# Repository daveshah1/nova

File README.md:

nova
====

This is the primary git repository for Team Nova's CanSat project, containing base station software, rover software, electronics and CAD data.

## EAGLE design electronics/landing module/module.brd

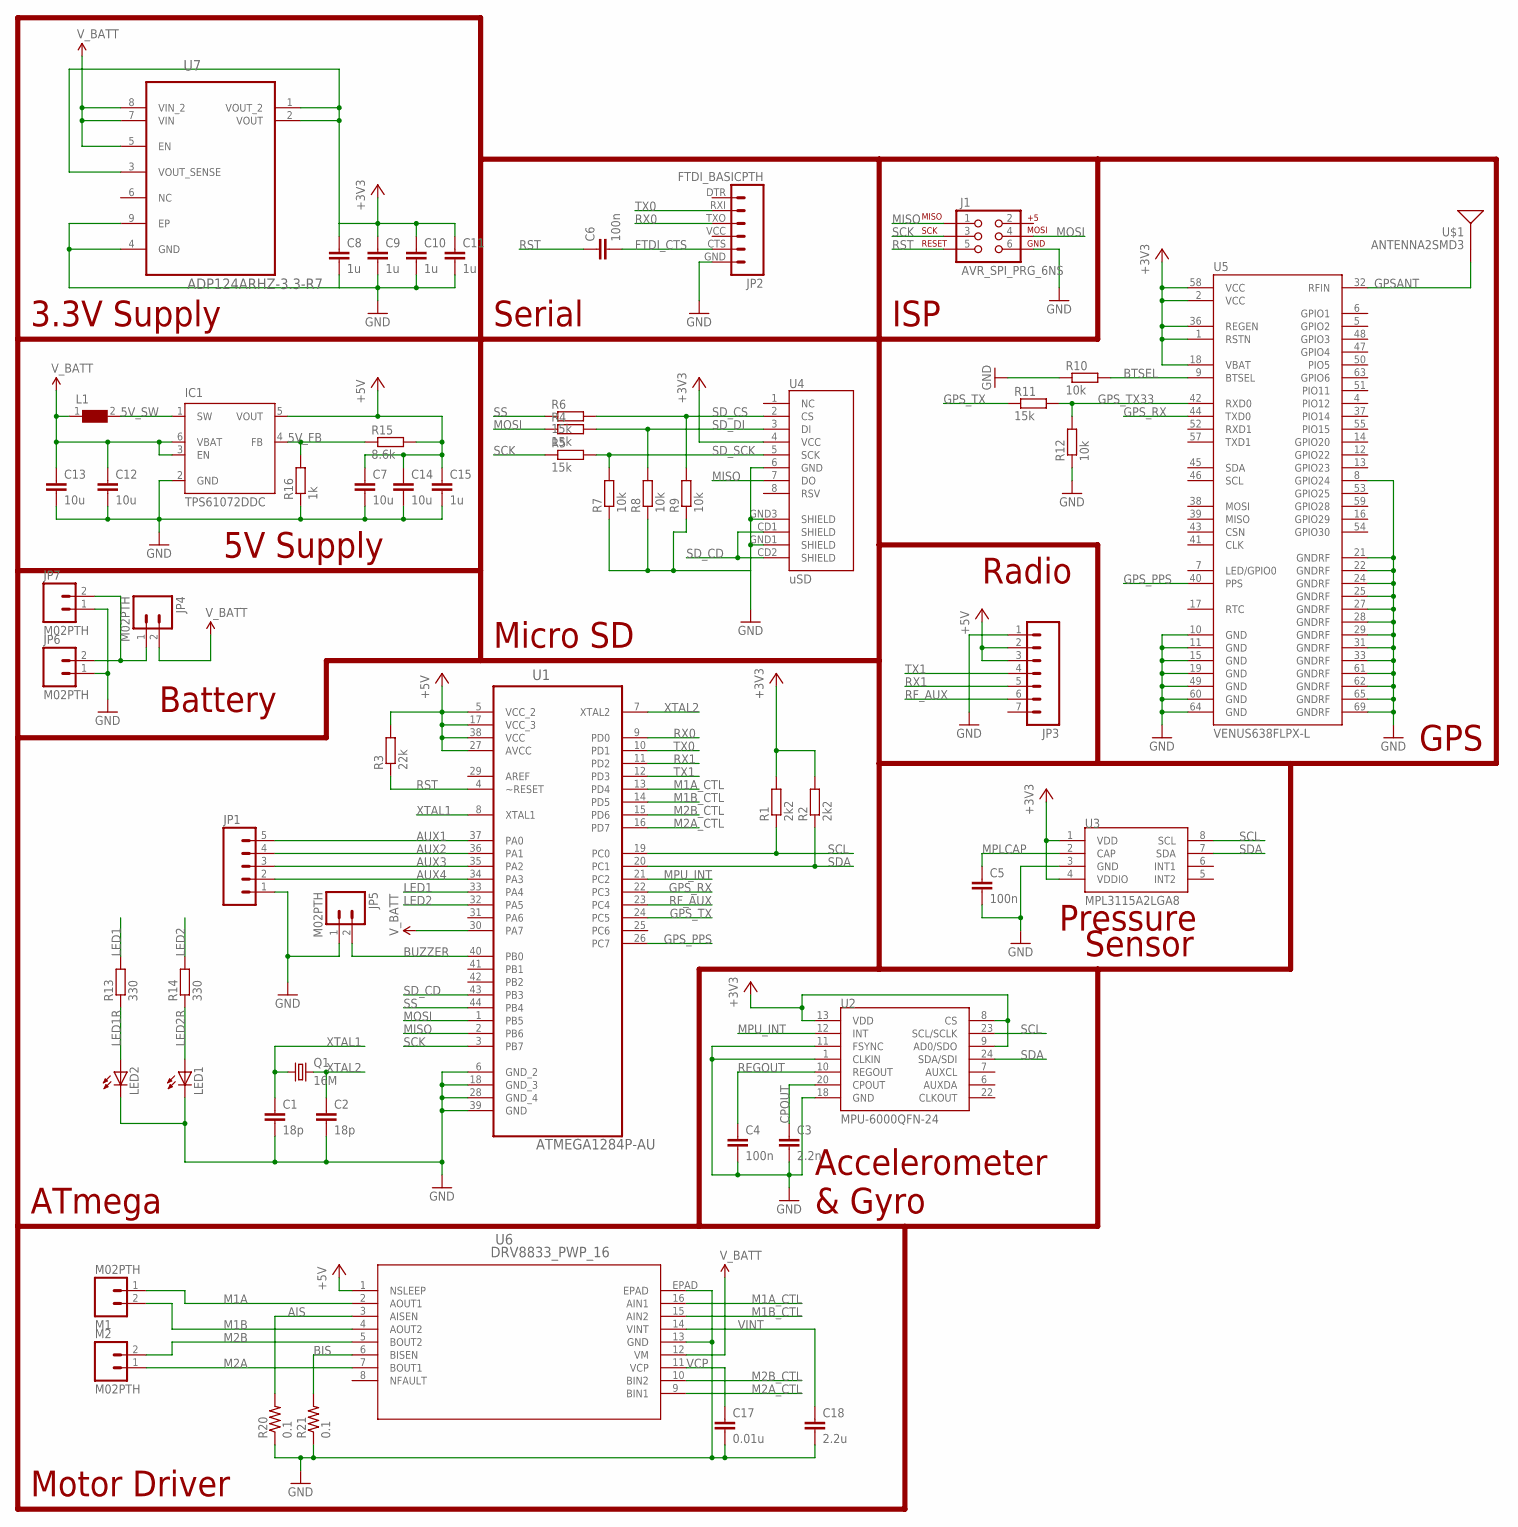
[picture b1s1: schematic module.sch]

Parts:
C1, C2: 18p; C0805
C3: 2.2n; C0805
C4, C5, C6: 100n; C0805
C7, C12, C13, C14: 10u; C0805
C8, C9, C10, C11: 1u; C0603
C15: 1u; C0805
C17: 0.01u; 0805
C18: 2.2u; 0805
IC1: TPS61072DDC; TSOT23-6_DDC
J1: AVR_SPI_PRG_6NS; 2X3-NS
JP1: M05PTH; 1X05
JP2: FTDI_BASICPTH; FTDI_BASIC
JP3: M07; 1X07
JP4, JP5, JP6, JP7: M02PTH; 1X02
L1: WE-TPC-744031004_3816; WE-TPC_3816
LED1, LED2: LEDCHIPLED_0805; CHIPLED_0805
M1, M2: M02PTH; 1X02
Q1: 16M; HC49UP
R1, R2: 2k2; R0805
R3: 22k; R0805
R4, R5, R6, R11: 15k; R0805
R7, R8, R9, R10, R12: 10k; R0805
R13, R14: 330; R0805
R15: 8.6k; R0805
R16: 1k; R0805
R20, R21: 0.1; 1206
U1: ATMEGA1284P-AU; QFP80P1200X1200X120-44N
U2: MPU-6000QFN-24; QFN-24-TESTING
U3: MPL3115A2LGA8; LGA8
U4: uSD; MICRO-SD-SOCKET-PP
U5: VENUS638FLPX-L; VENUS638FLPX
U6: DRV8833_PWP_16; PWP16_2P31X2P46
U7: ADP124ARHZ-3.3-R7; SOP65P490X110-9N
U$1: ANTENNA2SMD3; ANTENNA-CHIP4

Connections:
5V_FB: IC1.4 (FB), R15.1, R16.2
5V_SW: IC1.1 (SW), L1.2
+3V3: C8.1, C9.1, C10.1, C11.1, R1.2, R2.2, U2.8 (CS), U2.9 (AD0/SDO), U2.13 (VDD), U3.1 (VDD), U3.4 (VDDIO), U4.4 (VCC), U5.1 (RSTN), U5.2 (VCC), U5.18 (VBAT), U5.36 (REGEN), U5.58 (VCC), U7.1 (VOUT_2), U7.2 (VOUT), U7.3 (VOUT_SENSE)
+5V: C7.1, C14.1, C15.1, IC1.5 (VOUT), JP3.2, JP3.3, R3.2, R15.2, U1.5 (VCC_2), U1.17 (VCC_3), U1.27 (AVCC), U1.38 (VCC), U6.1 (NSLEEP)
AIS: R20.2, U6.3 (AISEN)
AUX1: JP1.5, U1.37 (PA0)
AUX2: JP1.4, U1.36 (PA1)
AUX3: JP1.3, U1.35 (PA2)
AUX4: JP1.2, U1.34 (PA3)
BIS: R21.2, U6.6 (BISEN)
BTSEL: R10.2, U5.9 (BTSEL)
BUZZER: JP5.2, U1.40 (PB0)
CPOUT: C3.1, U2.20 (CPOUT)
FTDI_CTS: C6.2, JP2.CTS (5)
GND: C1.2, C2.2, C3.2, C4.2, C5.2, C7.2, C8.2, C9.2, C10.2, C11.2, C12.2, C13.2, C14.2, C15.2, C17.2, C18.2, IC1.2 (GND), J1.6, JP1.1, JP2.GND (6), JP3.1, JP5.1, JP6.1, JP7.1, LED1.C, LED2.C, R7.1, R8.1, R9.1, R10.1, R12.1, R16.1, R20.1, R21.1, U1.6 (GND_2), U1.18 (GND_3), U1.28 (GND_4), U1.39 (GND), U2.1 (CLKIN), U2.11 (FSYNC), U2.18 (GND), U3.3 (GND), U4.6 (GND), U4.GND1 (SHIELD), U4.GND3 (SHIELD), U5.8 (GPIO24), U5.10 (GND), U5.11 (GND), U5.15 (GND), U5.19 (GND), U5.21 (GNDRF), U5.22 (GNDRF), U5.24 (GNDRF), U5.25 (GNDRF), U5.27 (GNDRF), U5.28 (GNDRF), U5.29 (GNDRF), U5.31 (GNDRF), U5.33 (GNDRF), U5.49 (GND), U5.60 (GND), U5.61 (GNDRF), U5.62 (GNDRF), U5.64 (GND), U5.65 (GNDRF), U5.69 (GNDRF), U6.13 (GND), U6.EPAD, U7.4 (GND), U7.9 (EP)
GPSANT: U5.32 (RFIN), U$1.SIG
GPS_PPS: U1.26 (PC7), U5.40 (PPS)
GPS_RX: U1.22 (PC3), U5.44 (TXD0)
GPS_TX: R11.1, U1.24 (PC5)
GPS_TX33: R11.2, R12.2, U5.42 (RXD0)
LED1: R13.2, U1.33 (PA4)
LED1R: LED2.A, R13.1
LED2: R14.2, U1.32 (PA5)
LED2R: LED1.A, R14.1
M1A: M1.1, U6.2 (AOUT1)
M1A_CTL: U1.13 (PD4), U6.16 (AIN1)
M1B: M1.2, U6.4 (AOUT2)
M1B_CTL: U1.14 (PD5), U6.15 (AIN2)
M2A: M2.1, U6.7 (BOUT1)
M2A_CTL: U1.16 (PD7), U6.9 (BIN1)
M2B: M2.2, U6.5 (BOUT2)
M2B_CTL: U1.15 (PD6), U6.10 (BIN2)
MISO: J1.1, U1.2 (PB6), U4.7 (DO)
MOSI: J1.4, R4.1, U1.1 (PB5)
MPLCAP: C5.1, U3.2 (CAP)
MPU_INT: U1.21 (PC2), U2.12 (INT)
unnamed: JP4.1, JP6.2, JP7.2
REGOUT: C4.1, U2.10 (REGOUT)
RF_AUX: JP3.6, U1.23 (PC4)
RST: C6.1, J1.5, R3.1, U1.4 (~RESET)
RX0: JP2.TXO (3), U1.9 (PD0)
RX1: JP3.5, U1.11 (PD2)
SCK: J1.3, R5.1, U1.3 (PB7)
SCL: R1.1, U1.19 (PC0), U2.23 (SCL/SCLK), U3.8 (SCL)
SDA: R2.1, U1.20 (PC1), U2.24 (SDA/SDI), U3.7 (SDA)
SD_CD: U1.43 (PB3), U4.CD1 (SHIELD), U4.CD2 (SHIELD)
SD_CS: R6.2, R9.2, U4.2 (CS)
SD_DI: R4.2, R8.2, U4.3 (DI)
SD_SCK: R5.2, R7.2, U4.5 (SCK)
SS: R6.1, U1.44 (PB4)
TX0: JP2.RXI (2), U1.10 (PD1)
TX1: JP3.4, U1.12 (PD3)
VCP: C17.1, U6.11 (VCP)
VINT: C18.1, U6.14 (VINT)
V_BATT: C12.1, C13.1, IC1.3 (EN), IC1.6 (VBAT), JP4.2, L1.1, U1.30 (PA7), U6.12 (VM), U7.5 (EN), U7.7 (VIN), U7.8 (VIN_2)
XTAL1: C1.1, Q1.1, U1.8 (XTAL1)
XTAL2: C2.1, Q1.2, U1.7 (XTAL2)

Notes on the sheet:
Motor Driver
ATmega
Pressure
Sensor
GPS
Radio
Micro SD
Battery
5V Supply
3.3V Supply
Serial
ISP
Accelerometer & Gyro

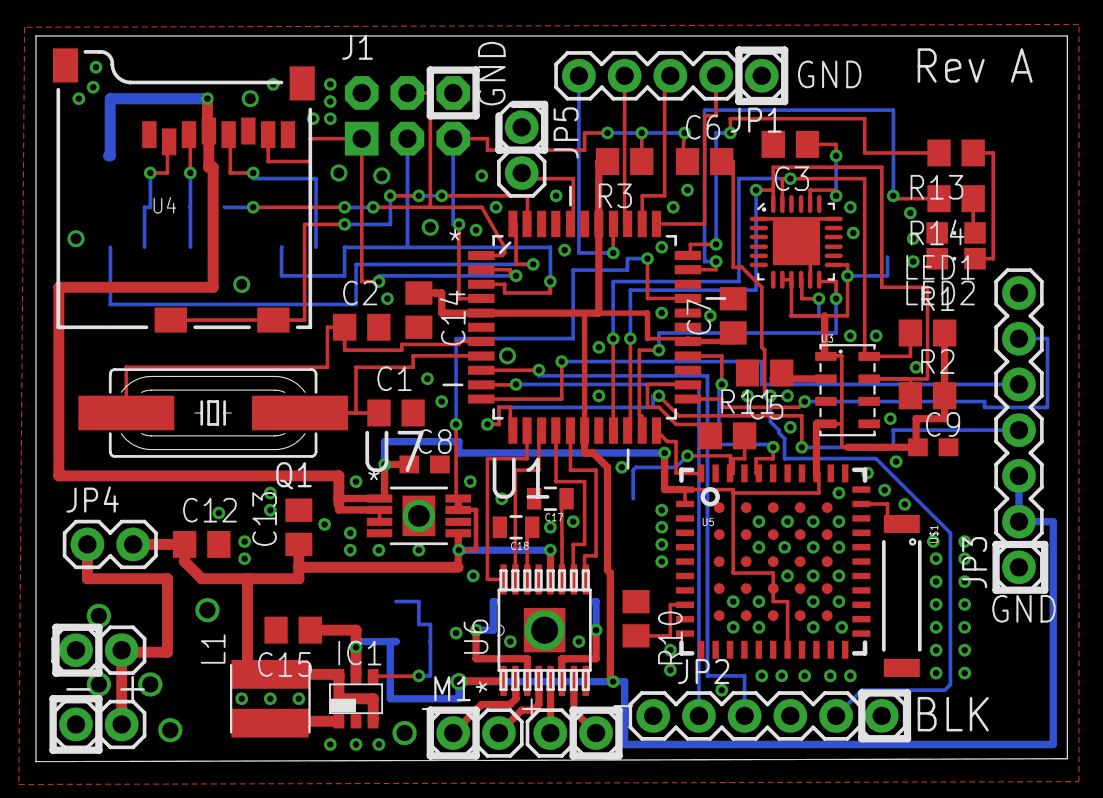
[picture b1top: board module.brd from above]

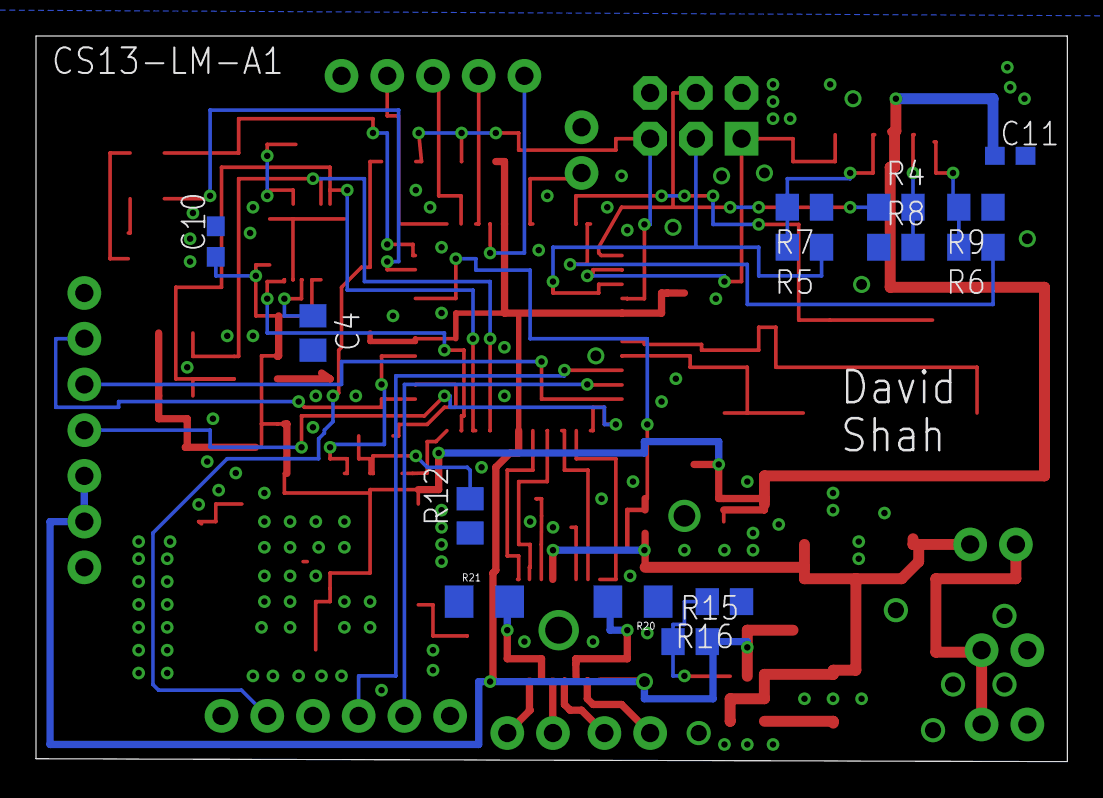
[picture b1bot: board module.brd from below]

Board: 2 copper layers, 57.3 x 40.3 mm, 58 parts (14 on the bottom side), 57 nets.

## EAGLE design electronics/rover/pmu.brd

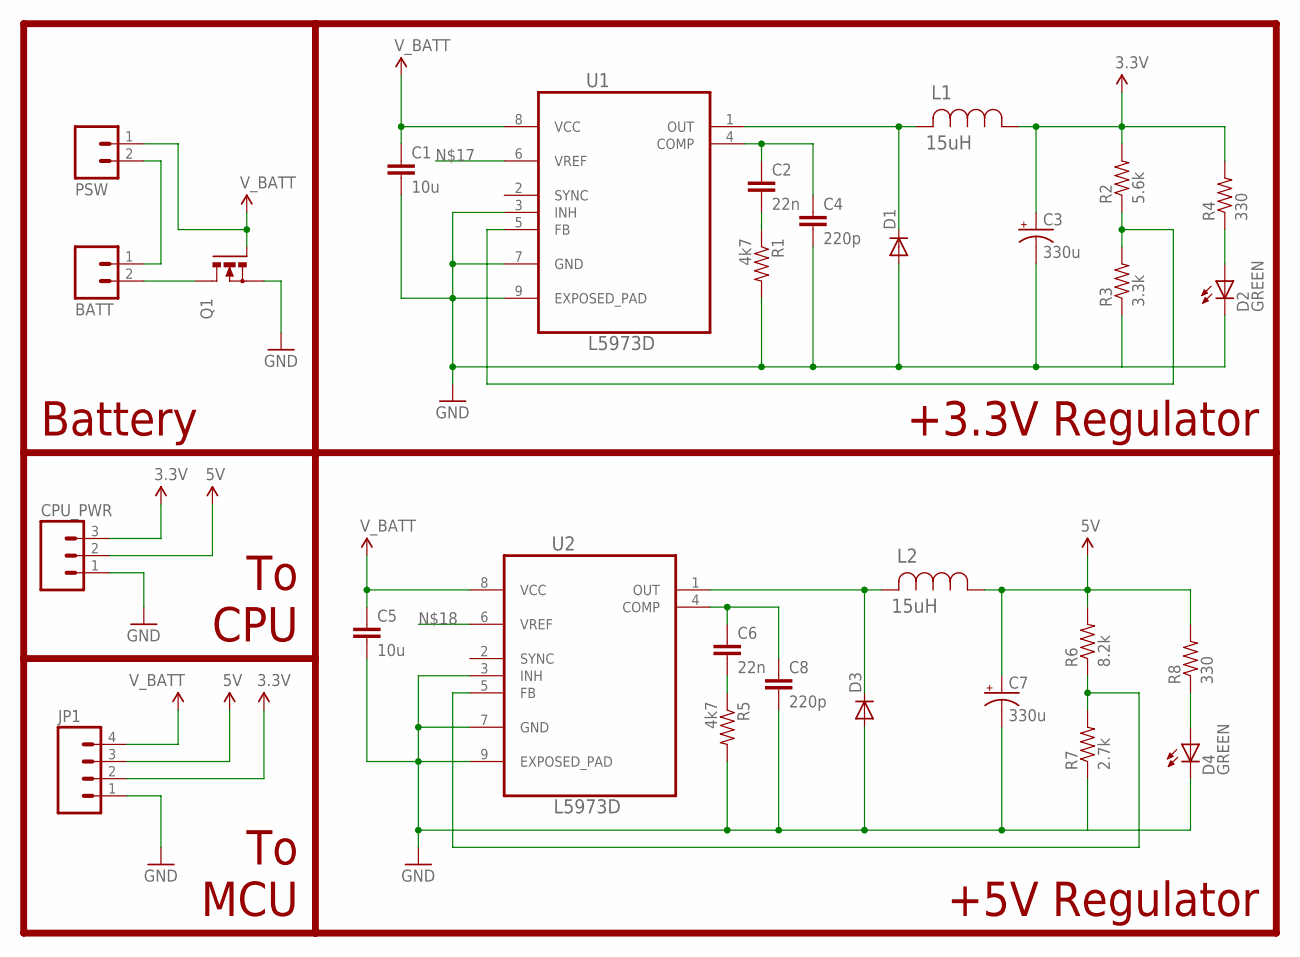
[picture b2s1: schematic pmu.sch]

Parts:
BATT: M02PTH; 1X02
C1, C5: 10u; 1210
C2, C6: 22n; 0805
C3, C7: 330u; EIA7343
C4, C8: 220p; 0805
CPU_PWR: M03PTH; 1X03
D1, D3: DIODESMB; SMB-DIODE
D2, D4: GREEN; CHIP-LED0805
JP1: M04PTH; 1X04
L1, L2: 15uH; IND_ELL8TP
PSW: M02PTH; 1X02
Q1: N-MOSFET-SO8S; SO-08
R1, R5: 4k7; 0805
R2: 5.6k; 0805
R3: 3.3k; 0805
R4, R8: 330; 0805
R6: 8.2k; 0805
R7: 2.7k; 0805
U1, U2: L5973D; SOP127P600X170-9N

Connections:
3.3V: C3.A (+), CPU_PWR.3, JP1.2, L1.1, R2.2, R4.2
5V: C7.A (+), CPU_PWR.2, JP1.3, L2.1, R6.2, R8.2
GND: C1.2, C3.C (-), C4.2, C5.2, C7.C (-), C8.2, CPU_PWR.1, D1.A, D2.C, D3.A, D4.C, JP1.1, Q1.1 (S), Q1.2 (S), Q1.3 (S), R1.2, R3.1, R5.2, R7.1, U1.3 (INH), U1.7 (GND), U1.9 (EXPOSED_PAD), U2.3 (INH), U2.7 (GND), U2.9 (EXPOSED_PAD)
unnamed: C2.1, C4.1, U1.4 (COMP)
unnamed: C2.2, R1.1
unnamed: D1.C, L1.2, U1.1 (OUT)
unnamed: BATT.2, Q1.5 (D), Q1.6 (D), Q1.7 (D), Q1.8 (D)
unnamed: R2.1, R3.2, U1.5 (FB)
unnamed: D2.A, R4.1
unnamed: C6.1, C8.1, U2.4 (COMP)
unnamed: C6.2, R5.1
unnamed: D3.C, L2.2, U2.1 (OUT)
unnamed: R6.1, R7.2, U2.5 (FB)
unnamed: D4.A, R8.1
unnamed: BATT.1, PSW.2
V_BATT: C1.1, C5.1, JP1.4, PSW.1, Q1.4 (G), U1.8 (VCC), U2.8 (VCC)

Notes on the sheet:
Battery
To CPU
To MCU
+3.3V Regulator
+5V Regulator

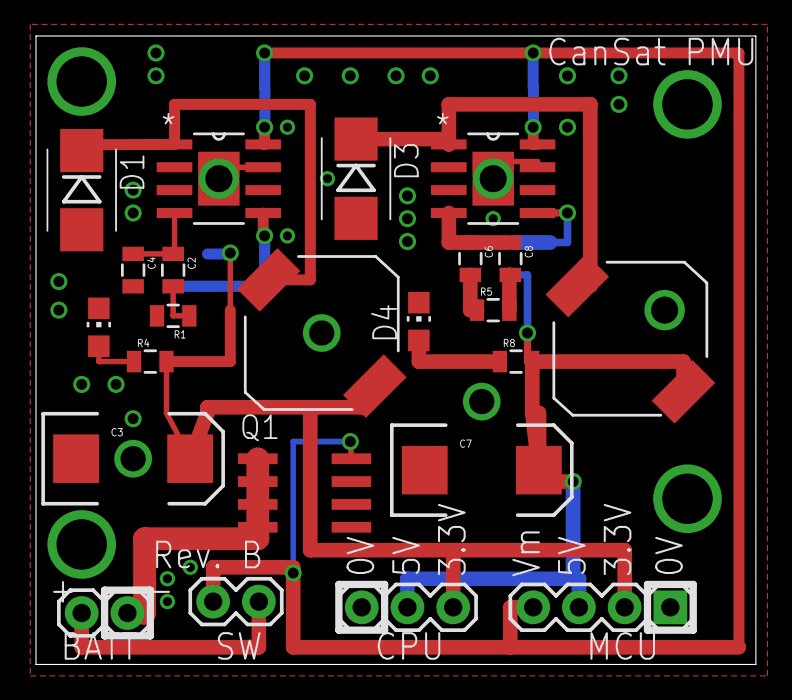
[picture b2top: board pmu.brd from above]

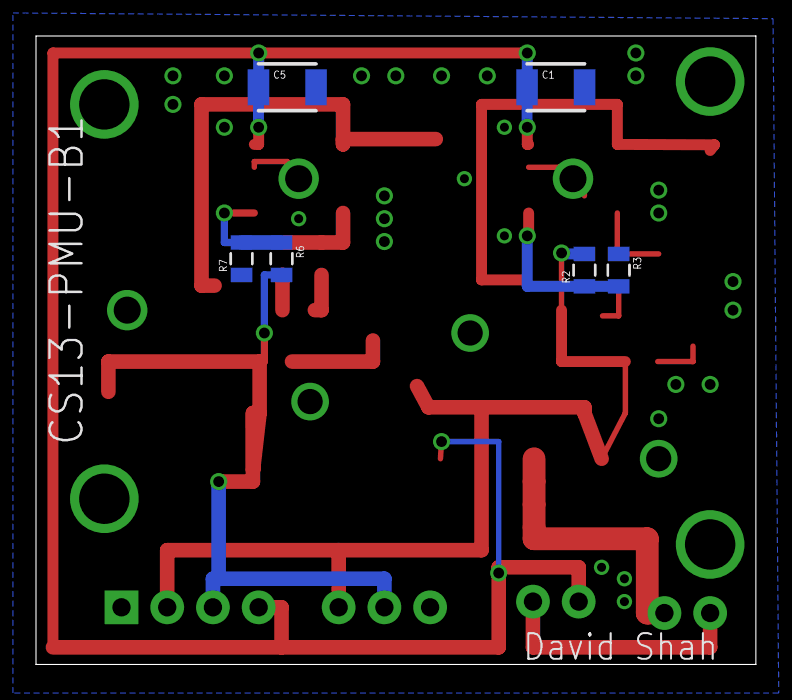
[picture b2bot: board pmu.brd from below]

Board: 2 copper layers, 40.0 x 34.9 mm, 29 parts (6 on the bottom side), 16 nets.

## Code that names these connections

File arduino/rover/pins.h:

//Motors
#define M1A_CTL 6
#define M1B_CTL 9
#define M2A_CTL 10
#define M2B_CTL 5

//Analog inputs
#define VBAT A0

//Status monitoring
#define PIEZO 7
#define STAT_LED A2

//Communications
#define LNK_MOSI 0
#define LNK_MISO 1
#define LNK_RDY  A1

#define POD_MISO 4
#define POD_MOSI 8

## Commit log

2013-09-23 Added Eagle schematics & PCBs
2013-09-23 Added basic Arduino program
2013-09-24 More Arduino test code
2013-09-24 Added pressure/temperature test code
2013-09-24 Modified pressure/temperature code
2013-09-25 Development Environment notes
    Update java to the following specs
2013-09-25 Initialisation of Experimental.GUI
    read the title!
2013-09-25 Revert "Meh"
    This reverts commit 564270c3b118b66e3fe7e008a8d5d9082352564a.
2013-09-25 Revert
2013-09-26 Debug section placeholder
2013-09-26 Added arduino serial packet comms library
2013-09-27 Added getCommand function to serial packet library
2013-09-27 Fixed getCommand, added getPayload
2013-09-27 Remove shizz
2013-09-27 Configured gitattributes
2013-09-27 Added sendReply fuction to serial packet library
2013-09-27 Function prototypes for BMP085 library
    Based on code from http://sensorapp.net/?p=278
2013-09-27 Added BMP085 library
    Based on code from http://sensorapp.net/?p=278
2013-09-27 Minor tweaks to SerialPacket code
2013-09-27 Added Arduino makefile
2013-09-28 Minor tweaks to gitignore
2013-09-28 More work on the Arduino code
2013-09-28 Changed to a different BMP085 library
2013-09-28 Added motor control to arduino code
2013-09-30 Added error checking to main.ino
2013-10-02 Fixed annoying error
2013-10-02 2nd experimental
    derpderpderp fix
2013-10-02 VERSION UPDATE: 0.0.0pre0.2 COMMIT
    Updated to version 0.0.0pre0.2
2013-10-02 getMap API: What should I do regarding google
2013-10-02 Cleaned up getMap
2013-10-02 Tidied up Arduino code
2013-10-05 Moved to OpenStreetMap
    This will allow mapping offline
    Includes JMapViewer with offline support from
    https://github.com/balloob/JMapViewer
    This deprecates the getMap class. Please read README-maps.txt before
    use.
2013-10-05 Added MapClickHandler
2013-10-05 Added a virtual rover
    Click on the map for a demo of interactive maps
2013-10-06 Removed Java bytecode
2013-10-06 Added build file for Apache Maven
2013-10-06 Added ant build files
    - Also several fixes & tweaks to the Java code.
    - Now ready for continuous integration
2013-10-09 Added yes/no option to MapClickHandler
    Also removed compiled class files
2013-10-09 Removed some obselete code
2013-10-09 Added position class with distance function
2013-10-09 Integrated Position class in main code
    Distances may not be very accurate (+/-10m) due to errors in the
    algorithm caused by the non-spherical nature of the Earth.
2013-10-10 Added RoverUpdateListener & Rover classes
    Rover class is a generic rover handling listener calling
    RoverUpdateListener is an interface for a handler for rover position and
    status updates.
2013-10-10 Worked on LargeMap
2013-10-10 Fixed LargeMap
2013-10-10 Added CustomMap class
2013-10-10 Cleaned up code to remove Eclipse warnings
2013-10-10 Added proper controls
2013-10-10 Improved control buttons
    - Now correctly arranged
    - Also more correct naming (i.e. North/South instead of Up/Down)
2013-10-11 Meh - fixed shizz
2013-10-11 Removed compiled class files
2013-10-12 Added Console class
2013-10-12 Improved control buttons, Improved spring layout
2013-10-13 Added functional controls
2013-10-15 Added move confirmations
2013-10-15 Moved location data to raw data
    Also added data type so graph plots can be distinguished
2013-11-29 Added new electronic designs
2013-12-10 Changed SerialPacket to use static memory
    Should prevent any bugs occurring due to fragmentation following
    repeated allocation and deallocation of memory. Also means memory leaks
    should no longer be a threat.
2013-12-10 Added MPL3115A2 library
2013-12-10 Added pins.h to Arduino code
2013-12-11 Updated Arduino code for new hardware
2013-12-13 Worked on selftest routines
2013-12-29 Added more Arduino code
2013-12-29 Added initial networking code
2013-12-31 Further work on network code and marker behaviour
    Should make control of real rover easier.
2013-12-31 Added initial NetworkRover class
2014-01-01 Added position fetching and associated test code
2014-01-01 Added manual move operations to NetworkRover
2014-01-01 Added stopRover
2014-01-01 Added getTP and related functions/structures
2014-01-01 Added preliminary Gumstix-side code
2014-01-01 Added readTP and motor control to arduino.py
2014-01-03 Added handlers for network telemetry & control
    Passes syntax test, otherwise UNCHECKED
2014-01-18 Initial LM test code
2014-01-19 Started work on GPS code for Gumstix
2014-01-20 Added skeleton landing module code to client
2014-01-21 Added skeleton BaseStationCommunications class
2014-01-21 Added RXTX dependency
2014-01-21 Fixed ant buildfile Took several attempts due to classpath confusions.
2014-01-21 Landing module radio handling code
2014-01-22 Made CustomMap a LandingModuleListener
2014-01-24 Added NetworkImageViewer component
    Unfortunately true streaming video is too difficult on the gumstix side.
    This has been replaced by updating a picture every second or so and
    displaying this.
    Xuggler is now no longer a dependency.
2014-01-24 Added crosshair to image
2014-01-24 Improved NetworkRover error handling
2014-01-25 Improved general program behaviour
    Ready for automated update/install utility
2014-01-26 Added Go To dialog
2014-01-28 Improvements to mapping
2014-01-29 Added settings dialog (not yet functional)
2014-01-30 Embed RXTX jar in nova.jar
2014-01-31 Initial SettingsStore
2014-02-01 Implement SettingsStore
2014-02-02 Functional video streaming
2014-02-03 Improved network and serial code
2014-02-03 Fix 3a602a3
2014-02-04 Improve communications code
2014-02-04 Basic EEPROM code
2014-02-05 More EEPROM code
2014-02-05 Work on EEPROM code
2014-02-06 Finished EEPROM code
    Compiles fine, otherwise untested
2014-02-08 Fixed bugs in Arduino code
2014-02-13 More work on roverside code
2014-02-13 ***WORKING TELEMETRY AND MOTOR CONTROL***
2014-02-14 Added DataLogger Class
2014-02-20 Enhancements to gumstix-side code
2014-02-20 Add wireless management script
2014-02-21 Added distance and angle calculations
2014-02-21 Fix 2cf0705
2014-02-23 Miscellaneous code
2014-02-24 More navigation code
2014-02-24 Enhancements and fixes to navcode
2014-02-24 Added Landing Module Arduino Code
    Nearly finished. Partially tested.
2014-02-25 Landing module GPS code & FSM
2014-02-25 More LM code
2014-02-26 RF related code
2014-02-26 Added some compass & LCD code
2014-02-26 Base Station related code
2014-02-27 Deployment related code
2014-02-27 Added deployment override backend
2014-02-27 Fixes to base station serial code
    Includes C#-based sneaky workaround to serial communications
2014-02-28 Removed dependency on 2nd microswitch
2014-02-28 Added deployment controls
2014-02-28 Miscellaneous LM-related changes
2014-02-28 SPI reliability improvements
2014-03-01 Near-final rover code
2014-03-02 Minor tweaks to rover code
2014-03-02 Reliability improvements
2014-03-02 Angular calculation fix
2014-03-02 Deployment code fixes
2014-03-02 *** FINAL ROVER CODE ***
2014-03-03 Datalogging & EEPROM management
2014-03-04 Image rotation
2014-03-05 Add landingmodule display to LargeMap
2014-03-08 Last-minute revisions

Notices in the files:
parts and their libraries:
SparkFun-Sensors: Licensing: CC v3.0 Share-Alike You are welcome to use this library for commercial purposes.
